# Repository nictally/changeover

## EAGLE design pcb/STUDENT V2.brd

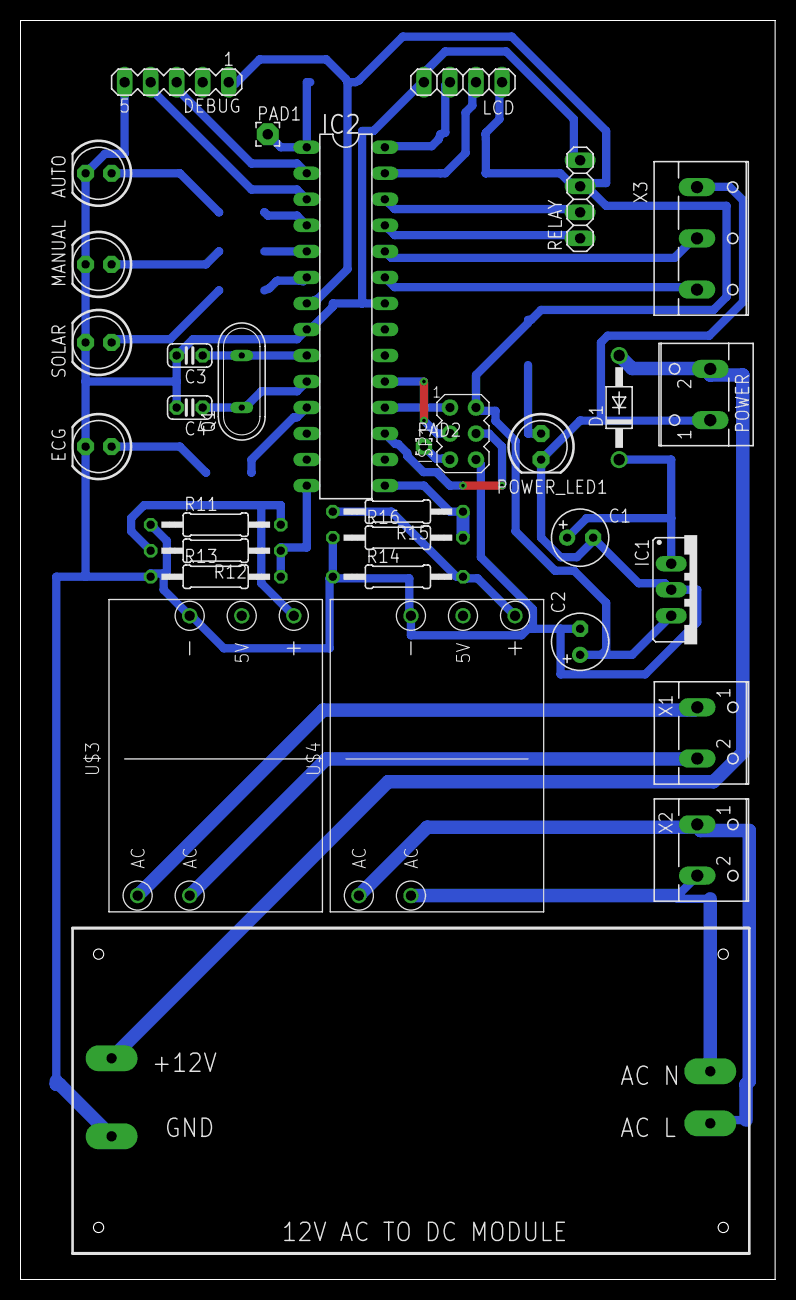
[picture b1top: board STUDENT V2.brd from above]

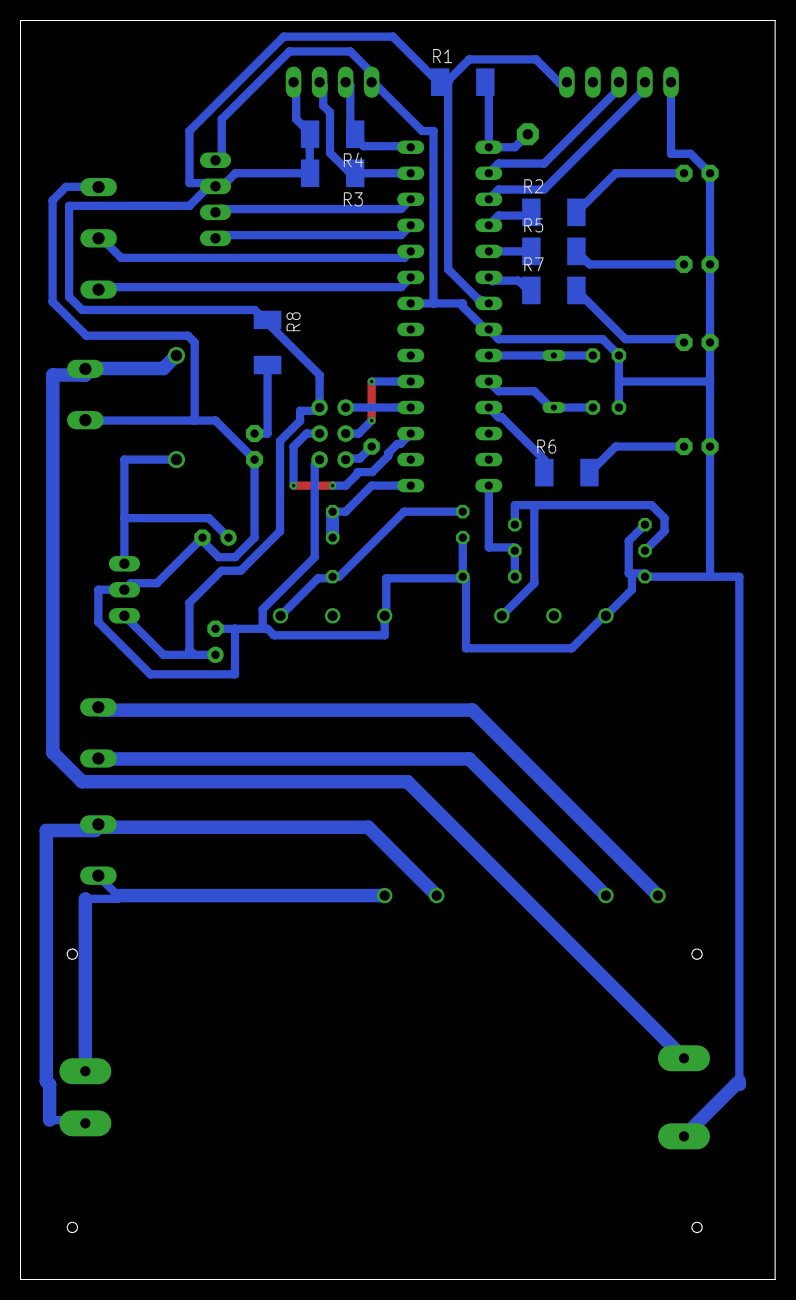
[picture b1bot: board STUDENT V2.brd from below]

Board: 2 copper layers, 73.6 x 122.9 mm, 40 parts (8 on the bottom side), 36 nets.

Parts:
AUTO: LED5MM
C1, C2: 100uF; E2,5-6
C3, C4: 22p; C025-024X044
D1: 1N4004; DO41-10
DEBUG: MA05-1
ECG: LED5MM
IC1: 78XXS
IC2: ATMEGA328-20P; DIL28-3
ISP1: AVRISP-6; AVRISP
LCD: 1X04
MANUAL: LED5MM
PAD1: WIREPAD2,15/1,0; 2,15/1,0
PAD2: WIREPAD1,6/0,8; 1,6/0,8
POWER: W237-102
POWER_LED1: LED5MM
Q1: 16MHz; QS
R1, R2, R3, R4, R5, R6, R7, R8: 10K; R2010
R11, R12, R13, R14, R15, R16: 10K; 0207/12
RELAY: 1X04
SOLAR: LED5MM
U$2: 12VMODULE12VMODULE; 12VMODULE
U$3, U$4: AC-DC-3.5W
X1, X2: W237-102
X3: W237-103

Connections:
+9V: D1.A, POWER.2, U$2.+12V
ACL: U$2.ACL, U$4.J1.1, X2.1
ACN: U$2.ACN, U$4.J1.2, X2.2
AUTO: IC2.4, R2.1
AUTO_SWITCH: IC2.24, X3.2
ECG: IC2.6, R7.1
GND: AUTO.K, C1.-, C2.-, C3.2, C4.2, DEBUG.5, ECG.K, IC1.GND, IC2.8, IC2.22, ISP1.6, LCD.4, MANUAL.K, POWER.1, POWER_LED1.K, R11.1, R13.1, R14.1, R16.1, RELAY.4, SOLAR.K, U$2.GND, U$3.J2.1, U$4.J2.1, X3.1
MANUAL: IC2.5, R5.1
MAN_SWITCH: IC2.23, X3.3
MISO: IC2.18, ISP1.1
MOSI: IC2.17, ISP1.4
unnamed: IC2.25, RELAY.1
unnamed: POWER_LED1.A, R8.2
unnamed: C3.1, IC2.9, Q1.2
unnamed: C4.1, IC2.10, Q1.1
unnamed: AUTO.A, R2.2
unnamed: C1.+, D1.C, IC1.IN
unnamed: MANUAL.A, R5.2
unnamed: ECG.A, R6.2
unnamed: R7.2, SOLAR.A
unnamed: R11.2, R12.2, U$3.J2.3
unnamed: R14.2, R15.2, U$4.J2.3
unnamed: U$3.J1.1, X1.1
unnamed: U$3.J1.2, X1.2
unnamed: IC2.26, RELAY.2
OUT1: IC2.14, R12.1, R13.2
OUT2: IC2.15, R15.1, R16.2
RST: IC2.1, PAD1.1, R1.2
RSTK: ISP1.5, PAD2.1
RXD: DEBUG.4, IC2.3
SCK: IC2.19, ISP1.3
SCL: IC2.28, LCD.3, R4.1
SDA: IC2.27, LCD.2, R3.1
SOLAR: IC2.11, R6.1
TXD: DEBUG.3, IC2.2
VCC: C2.+, DEBUG.1, IC1.OUT, IC2.7, ISP1.2, LCD.1, R1.1, R3.2, R4.2, R8.1, RELAY.3

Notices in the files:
parts and their libraries:
diy-modules: Released under the Creative Commons Attribution 4.0 International License: http://creativecommons.org/licenses/by/4.0
